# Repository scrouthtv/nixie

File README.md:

# About VFD tubes

<!---->

The manufacturer has a [good explanation of the concept of VFD tubes](http://futaba.co.jp/en/display/vfd/index.html) on their website.

They basically work like this:
1. A *filament* (usually a Tungsten wire) is heated up and emits electrons into the vacuum in the tube.
2. The electrons are accelerated through a *grid* towards a positive-charged *anode*.
3. The electrons collide with the phosphor-coated anode and emit light due to [fluorescence](https://en.wikipedia.org/wiki/Fluorescence).

In the simplest case, the anodes make up an 8-figure consisting of seven individual segments plus a decimal point as an eigth segment.
[More complicated designs](http://futaba.co.jp/en/display/vfd/applications.html) such as combining multiple letters of different size, adding in symbols or [colors](https://en.wikipedia.org/wiki/Phosphorescence#Materials).

Each anode has its own wire leaving the casing.
The whole tube must be "activated" by setting the grid to a higher potential compared to the filament, which allows for multiplexing multiple tubes.

Image Source: [VFD | Futaba Corporation](http://futaba.co.jp/en/display/vfd/index.html)

# The tubes

I recently got ten VFD tubes labelled as **Futaba DG10Q1 3GS** out of an old calculator that was due for trash:

The manufacturer has been ["selling gas-discharge display tube [since] 1968"](http://futaba.co.jp/en/files/notice_20200805.pdf). Sadly, they want to leave the business until the end of this year (2021).

The tubes themselves look fantastic:

Image Source: Used with permission, own work.

## Testing a tube

I wasn't able to find a datasheet online, only this image that circulates on the internet:

**Keep in mind that this is the bottom view.**

The filament in this tube is a thin wire in the front center that runs from the bottom to the top.
It glows orange-ish after applying a high enough current to it. 

My tubes have a set of red-colored wires for the filament. If yours don't, try to find the pair of pins wich has the lowest resistance (lower than 10 ohms). 

Slowly increasing the voltage across these two pins, they started glowing at around 0.8 V.

As a next step, I applied 18 V to both the grid and a segment to see it glowing.

Image Source: [DG10Q1 | AsahiNet](https://ne.jp/asahi/shared/o-family/ElecRoom/PARTS/DISPLAY/ElDG10Q1.html)

# My final circuit

I am planning on combining multiple tubes to get a "smart" clock which is controlled by an atmega328 chip (the chip that is also used in an Arduino).
The atmega can then be combined with a Raspberry Pi which controls the displayed text. 

In the end, I'll need at least a 5 V power supply for the logic.

## The filament driver

The filament basically carries all the load of the tube.
I found that a single DG10Q1 consumes up to 50 mA at 1 V!

The easiest way would be to use a voltage regulator which creates 1 V from my 5 V supply.
However, many common voltage regulators use a reference voltage of 1.25 V (e.g. [LM317](https://ti.com/lit/ds/symlink/lm317.pdf) or [MAX1733](https://datasheets.maximintegrated.com/en/ds/MAX1733-MAX1734.pdf)) and can't be adjusted to anything below 1.25 V ([without an overly complicated circuit](https://electronics.stackexchange.com/questions/116842/very-low-voltage-regulator?newreg=f15bd3da58fc4a10ab08af88b5f3e868)).

Because of this issue, I am using a type of [current mirror circuit](https://wiki.analog.com/university/courses/electronics/text/chapter-11) instead:

Technically, it is used to mirror the amps from an input to the output.

However, with the correct value for R3, an arbitrary output voltage can be set.

*TODO: this is not correct and needs more work*

Image source: Own work.

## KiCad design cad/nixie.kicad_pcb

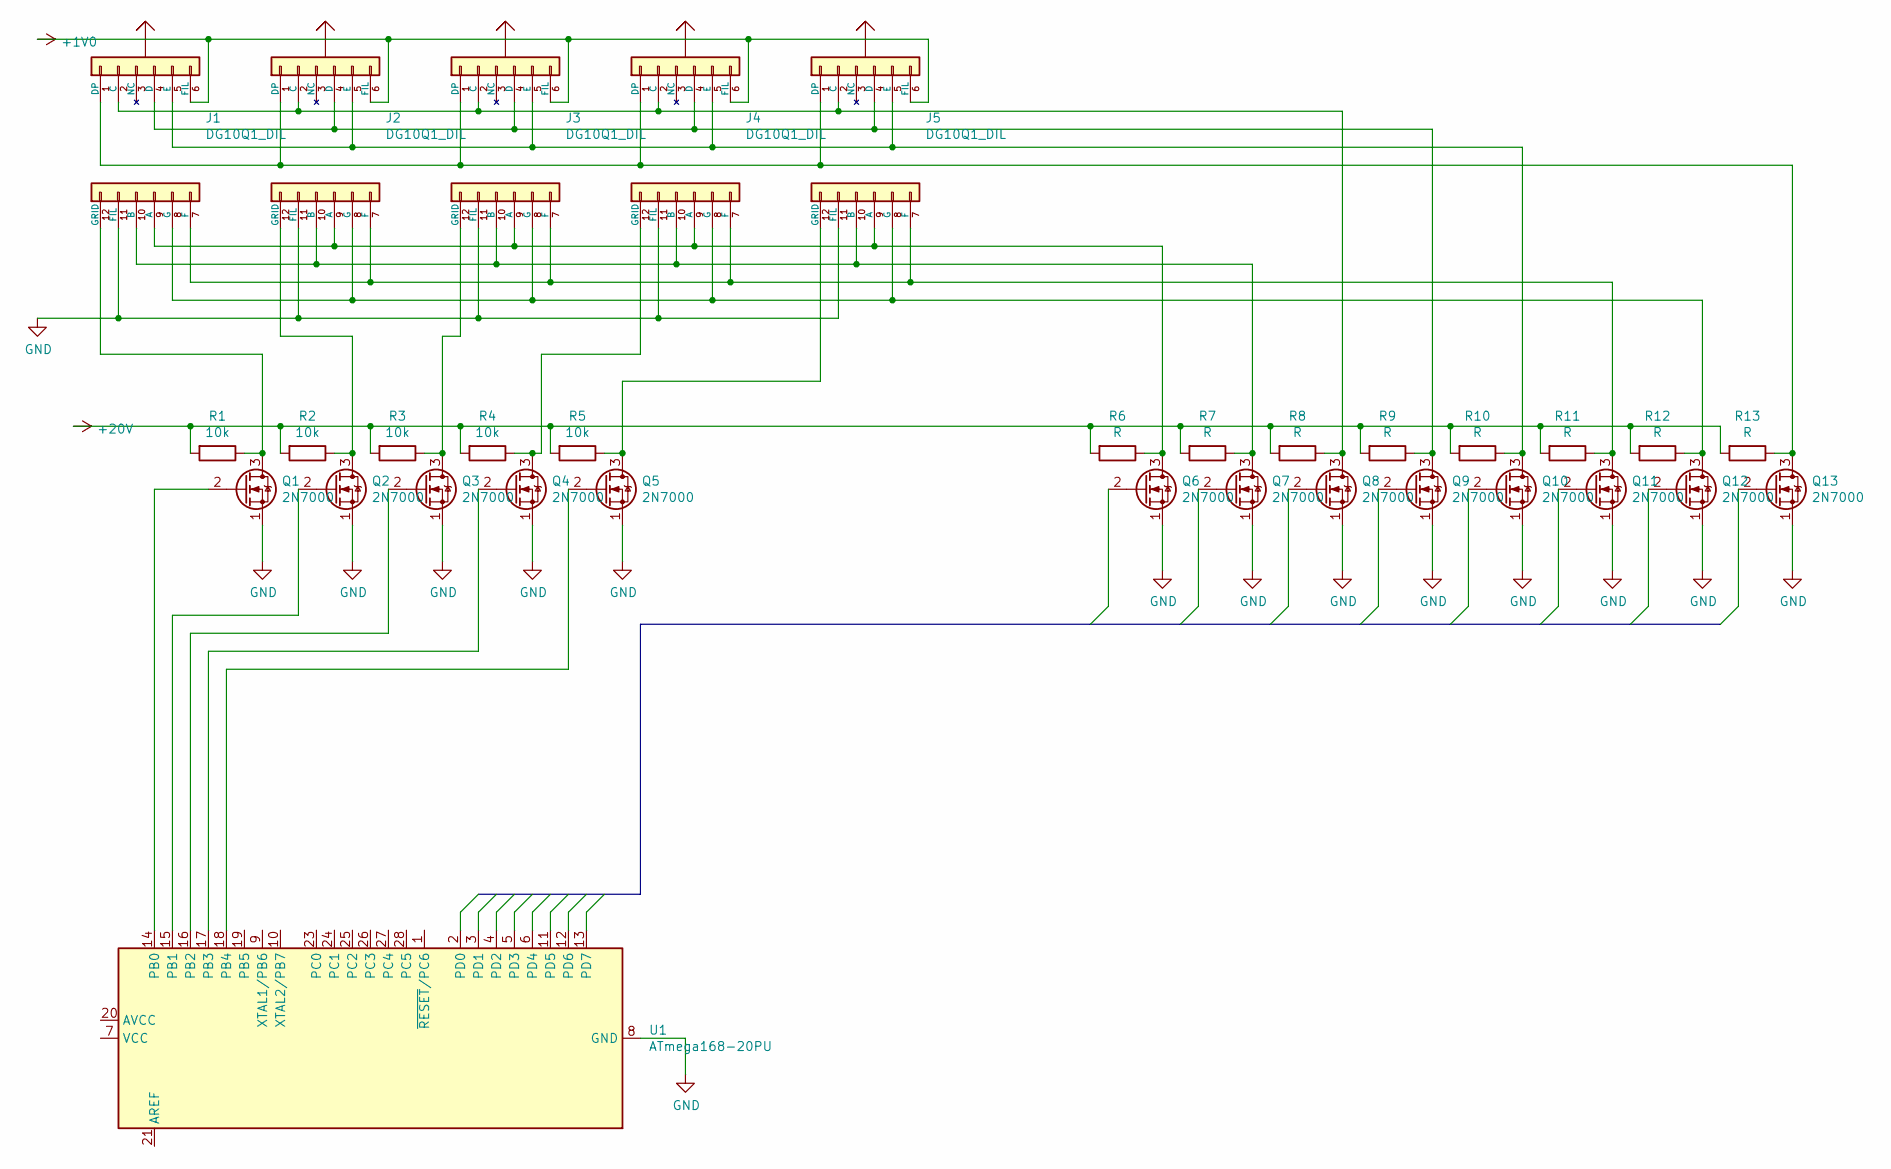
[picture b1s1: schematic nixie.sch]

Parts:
J1, J2, J3, J4, J5: DG10Q1_DIL; DG10Q1_DIL_2.54mm
Q1, Q2, Q3, Q4, Q5, Q6, Q7, Q8, Q9, Q10, Q11, Q12, Q13: 2N7000; TO-92_Inline
R1, R2, R3, R4, R5: 10k; R_Axial_DIN0207_L6.3mm_D2.5mm_P10.16mm_Horizontal
R6, R7, R8, R9, R10, R11, R12, R13: R; R_Axial_DIN0207_L6.3mm_D2.5mm_P10.16mm_Horizontal
U1: ATmega168-20PU; DIP-28_W7.62mm

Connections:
+1V0: J1.6 (FIL), J2.6 (FIL), J3.6 (FIL), J4.6 (FIL), J5.6 (FIL)
+20V: R1.2, R2.2, R3.2, R4.2, R5.2, R6.2, R7.2, R8.2, R9.2, R10.2, R11.2, R12.2, R13.2
GND: J1.11 (FIL), J2.11 (FIL), J3.11 (FIL), J4.11 (FIL), J5.11 (FIL), Q1.1 (S), Q2.1 (S), Q3.1 (S), Q4.1 (S), Q5.1 (S), Q6.1 (S), Q7.1 (S), Q8.1 (S), Q9.1 (S), Q10.1 (S), Q11.1 (S), Q12.1 (S), Q13.1 (S), U1.8 (GND), U1.22 (GND)
unnamed: J1.1 (DP), J2.1 (DP), J3.1 (DP), J4.1 (DP), J5.1 (DP), Q13.3 (D), R13.1
unnamed: J1.2 (C), J2.2 (C), J3.2 (C), J4.2 (C), J5.2 (C), Q8.3 (D), R8.1
unnamed: J1.4 (D), J2.4 (D), J3.4 (D), J4.4 (D), J5.4 (D), Q9.3 (D), R9.1
unnamed: J1.5 (E), J2.5 (E), J3.5 (E), J4.5 (E), J5.5 (E), Q10.3 (D), R10.1
unnamed: J1.7 (F), J2.7 (F), J3.7 (F), J4.7 (F), J5.7 (F), Q11.3 (D), R11.1
unnamed: J1.8 (G), J2.8 (G), J3.8 (G), J4.8 (G), J5.8 (G), Q12.3 (D), R12.1
unnamed: J1.9 (A), J2.9 (A), J3.9 (A), J4.9 (A), J5.9 (A), Q6.3 (D), R6.1
unnamed: J1.10 (B), J2.10 (B), J3.10 (B), J4.10 (B), J5.10 (B), Q7.3 (D), R7.1
unnamed: J1.12 (GRID), Q1.3 (D), R1.1
unnamed: J2.12 (GRID), Q2.3 (D), R2.1
unnamed: J3.12 (GRID), Q3.3 (D), R3.1
unnamed: J4.12 (GRID), Q4.3 (D), R4.1
unnamed: J5.12 (GRID), Q5.3 (D), R5.1
unnamed: Q1.2 (G), U1.14 (PB0)
unnamed: Q2.2 (G), U1.15 (PB1)
unnamed: Q3.2 (G), U1.16 (PB2)
unnamed: Q4.2 (G), U1.17 (PB3)
unnamed: Q5.2 (G), U1.18 (PB4)

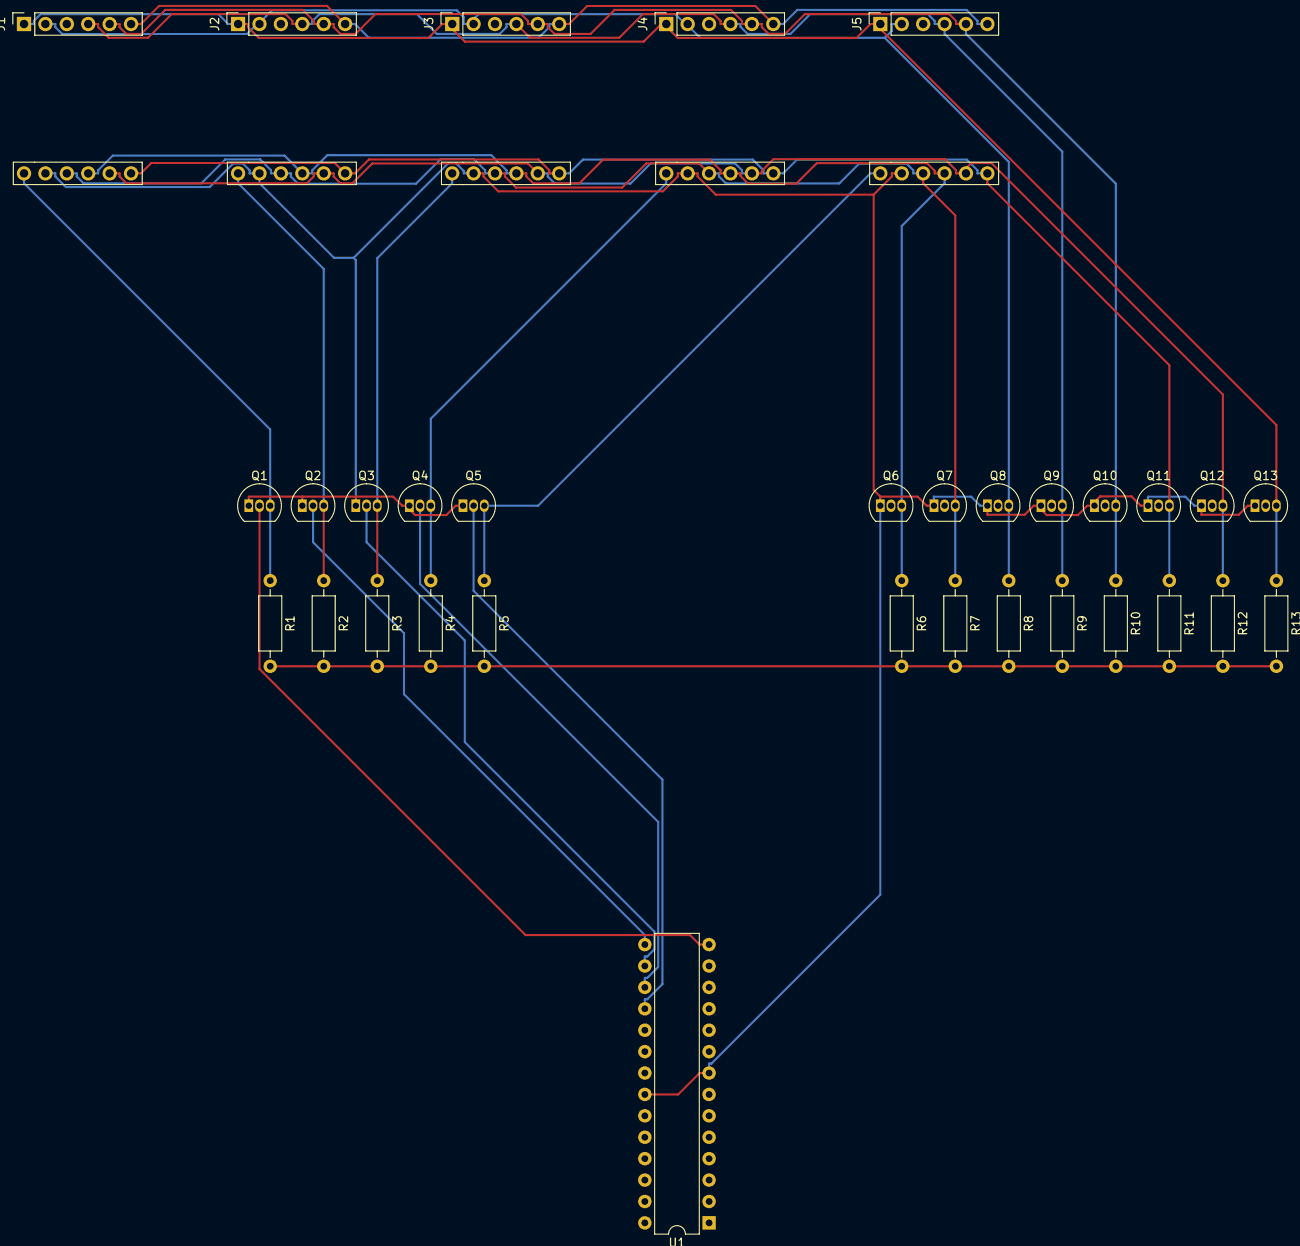
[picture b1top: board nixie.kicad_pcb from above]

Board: 2 copper layers, 32 parts (0 on the bottom side), 21 nets.

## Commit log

2021-03-17 kicad files v1
2021-03-17 two test programs
2021-03-17 first drawing
2021-03-17 makefile which creates pdf & svg
2021-03-17 drawing of the anode driver
2021-03-17 fixed weird margin
2021-03-24 filament driver
2021-03-24 blog pt 1
2021-03-24 further reading
2021-03-24 testing a tube
2021-03-24 fixed svg output
2021-03-24 Update README.md
    minor typo
